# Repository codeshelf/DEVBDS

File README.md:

# DEVBDS
All of the weird, awesome, strange and mundane dev boards one could ever hope to use.

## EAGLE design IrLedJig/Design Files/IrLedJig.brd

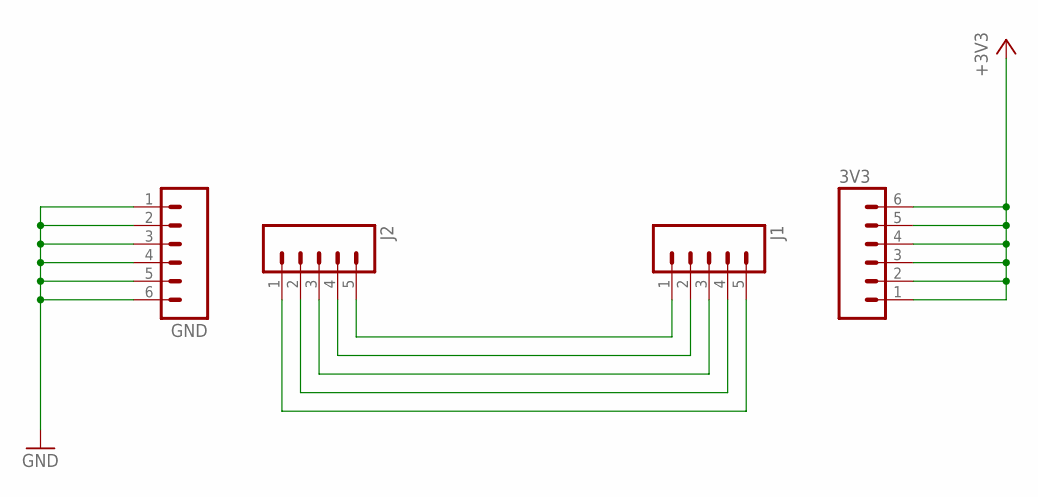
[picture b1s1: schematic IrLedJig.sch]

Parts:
3V3: M06LOCK; 1X06_LOCK
GND: M06LOCK; 1X06_LOCK
J1, J2: M05LOCK; 1X05_LOCK

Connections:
+3V3: 3V3.1, 3V3.2, 3V3.3, 3V3.4, 3V3.5, 3V3.6
GND: GND.1, GND.2, GND.3, GND.4, GND.5, GND.6
unnamed: J1.1, J2.5
unnamed: J1.2, J2.4
unnamed: J1.3, J2.3
unnamed: J1.4, J2.2
unnamed: J1.5, J2.1

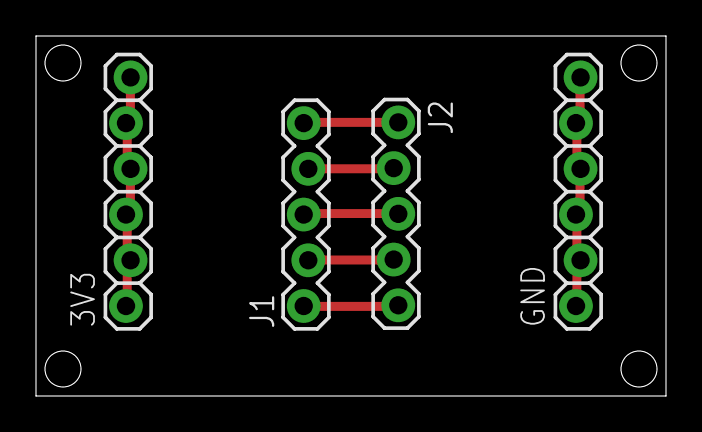
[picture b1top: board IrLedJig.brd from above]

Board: 2 copper layers, 35.0 x 20.0 mm, 4 parts (0 on the bottom side), 7 nets.

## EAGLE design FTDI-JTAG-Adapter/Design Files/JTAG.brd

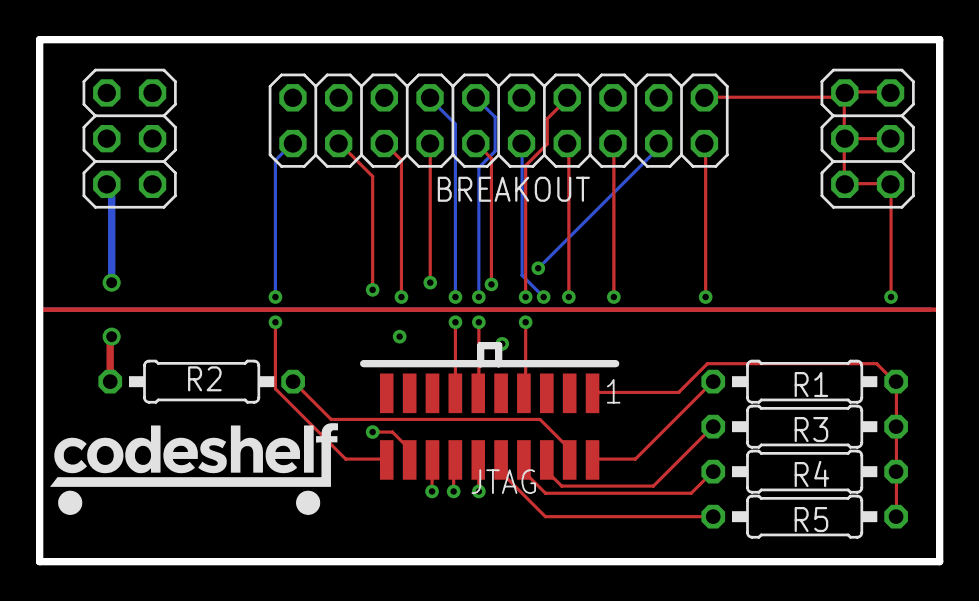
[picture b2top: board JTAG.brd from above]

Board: 4 copper layers, 50.0 x 29.0 mm, 10 parts (0 on the bottom side), 15 nets.

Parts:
3V3: 2X03
BREAKOUT: 2X10
GND: 2X03
JTAG: 2X10JTAGSMD; 2X10JTAG-SMD
R1, R2, R3, R4, R5: 0207/10
U$1: CODESHELF-LOGOSMALL; CODESHELF-LOGO-SMALL

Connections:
3V3: 3V3.1, 3V3.2, 3V3.3, 3V3.4, 3V3.5, 3V3.6, BREAKOUT.1, JTAG.P$1, R1.1, R3.1, R4.1, R5.1
GND: BREAKOUT.3, BREAKOUT.5, BREAKOUT.9, BREAKOUT.15, BREAKOUT.17, BREAKOUT.19, GND.1, GND.2, GND.3, GND.4, GND.5, GND.6, JTAG.P$3, JTAG.P$5, JTAG.P$9, JTAG.P$15, JTAG.P$17, JTAG.P$19, R2.1
unnamed: BREAKOUT.2, JTAG.P$2, R1.2
unnamed: BREAKOUT.4, JTAG.P$4, R2.2
unnamed: BREAKOUT.6, JTAG.P$6, R3.2
unnamed: BREAKOUT.8, JTAG.P$8, R4.2
unnamed: BREAKOUT.10, JTAG.P$10, R5.2
unnamed: BREAKOUT.12, JTAG.P$12
unnamed: BREAKOUT.14, JTAG.P$14
unnamed: BREAKOUT.16, JTAG.P$16
unnamed: BREAKOUT.18, JTAG.P$18
unnamed: BREAKOUT.20, JTAG.P$20
unnamed: BREAKOUT.7, JTAG.P$7
unnamed: BREAKOUT.11, JTAG.P$11
unnamed: BREAKOUT.13, JTAG.P$13

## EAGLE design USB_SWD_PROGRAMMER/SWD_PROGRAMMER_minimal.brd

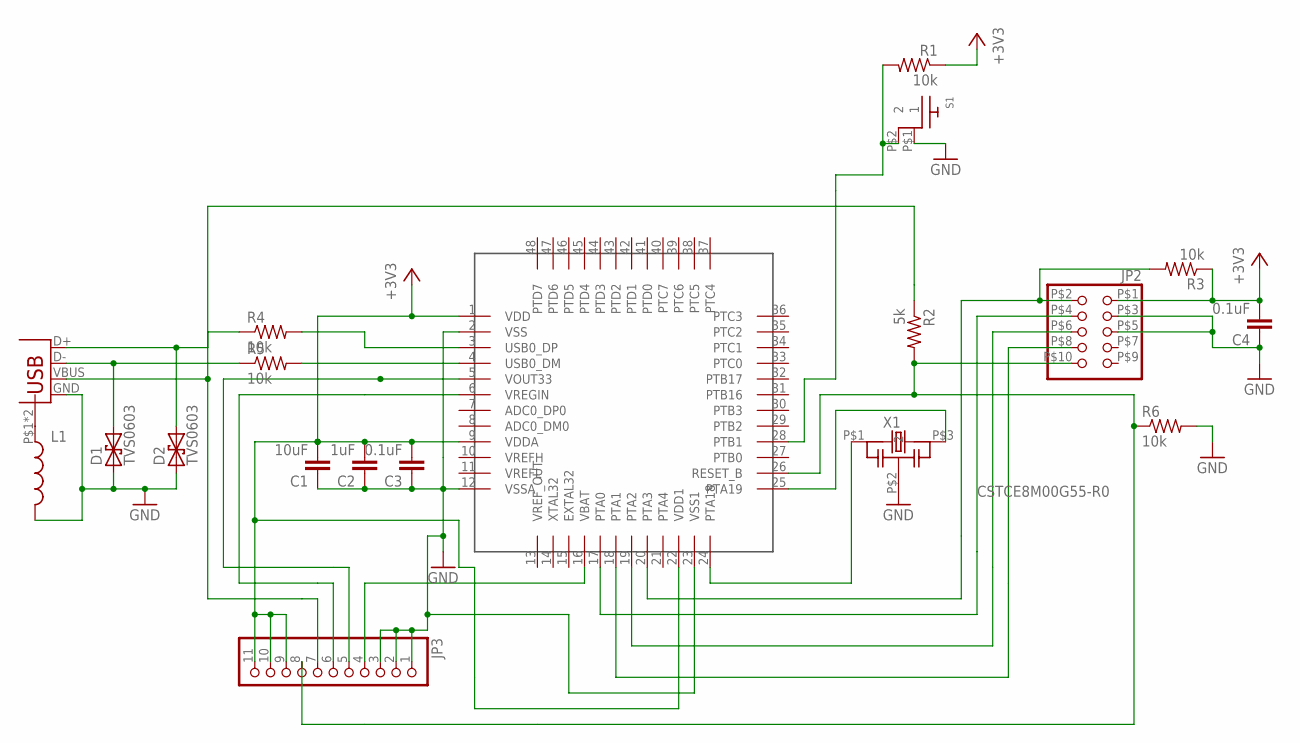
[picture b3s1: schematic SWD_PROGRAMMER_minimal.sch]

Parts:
C1: 10uF; C0805
C2: 1uF; C0805
C3, C4: 0.1uF; C0805
D1, D2: TVS0603; 0603-RES
J1: USB_B; USB-B-PTH-VERTICAL
JP2: PINHD-2X5SMALL; 2X5HDR
JP3: PINHD-1X11; 1X11
L1: INDUCTOR0603; 0603
R1, R3, R4, R5, R6: 10k; RF-C0805
R2: 5k; RF-C0805
S1: RA_BUTTON
U$1: KL20_48; LQFP-48
X1: CSTCE8M00G55-R0; CSTCE_G_A

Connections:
+3V3: C1.2, C2.2, C3.2, C4.2, JP2.P$1 (1), JP3.9, JP3.10, JP3.11, R1.1, R3.1, U$1.1 (VDD), U$1.9 (VDDA), U$1.22 (VDD1)
CLK: JP2.P$4 (4), U$1.17 (PTA0)
D_N: D1.2, J1.D-, R5.1
D_P: D2.2, J1.D+, R4.1
GND: C1.1, C2.1, C3.1, C4.1, D1.1, D2.1, J1.GND, JP2.P$3 (3), JP2.P$5 (5), JP3.1, JP3.2, JP3.3, L1.2, R6.2, S1.P$1 (1), U$1.2 (VSS), U$1.12 (VSSA), U$1.23 (VSS1), X1.P$2 (2)
JRST: JP2.P$10 (10), JP3.8, R2.2, R6.1, U$1.26 (RESET_B)
unnamed: R4.2, U$1.3 (USB0_DP)
unnamed: J1.VBUS, JP3.7, R2.1
unnamed: JP3.4, U$1.16 (VBAT)
unnamed: U$1.24 (PTA18), X1.P$1 (1)
unnamed: J1.P$1 (SHIELD), J1.P$2 (SHIELD), L1.1
unnamed: U$1.25 (PTA19), X1.P$3 (3)
unnamed: JP3.5, U$1.5 (VOUT33)
unnamed: JP3.6, U$1.6 (VREGIN)
unnamed: R5.2, U$1.4 (USB0_DM)
RST: R1.2, S1.P$2 (2), U$1.28 (PTB1)
TDI: JP2.P$8 (8), U$1.18 (PTA1)
TDO: JP2.P$6 (6), U$1.19 (PTA2)
TMS: JP2.P$2 (2), R3.2, U$1.20 (PTA3)

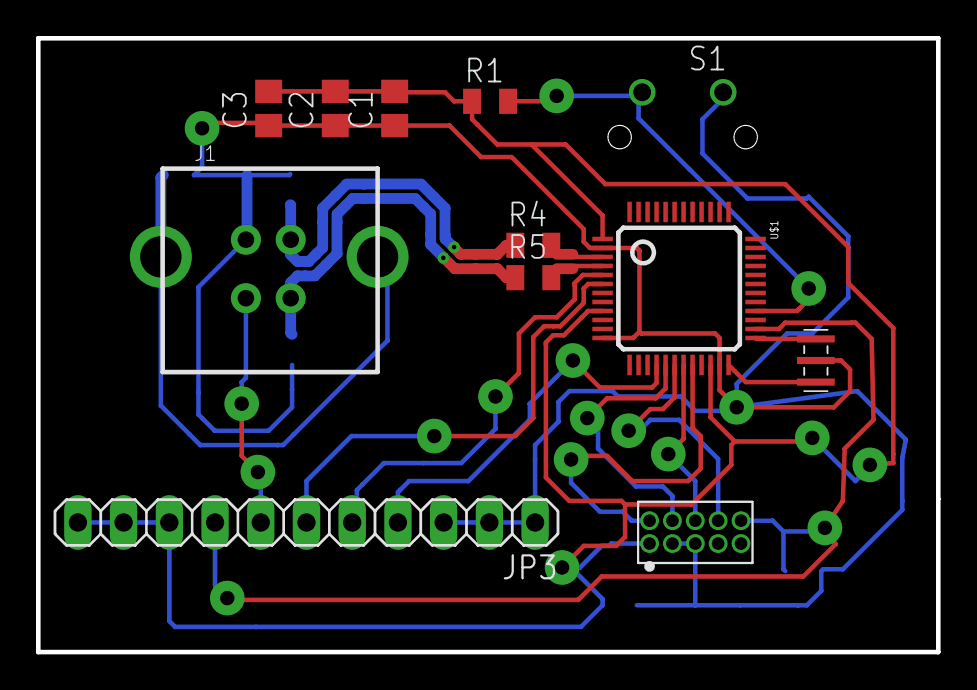
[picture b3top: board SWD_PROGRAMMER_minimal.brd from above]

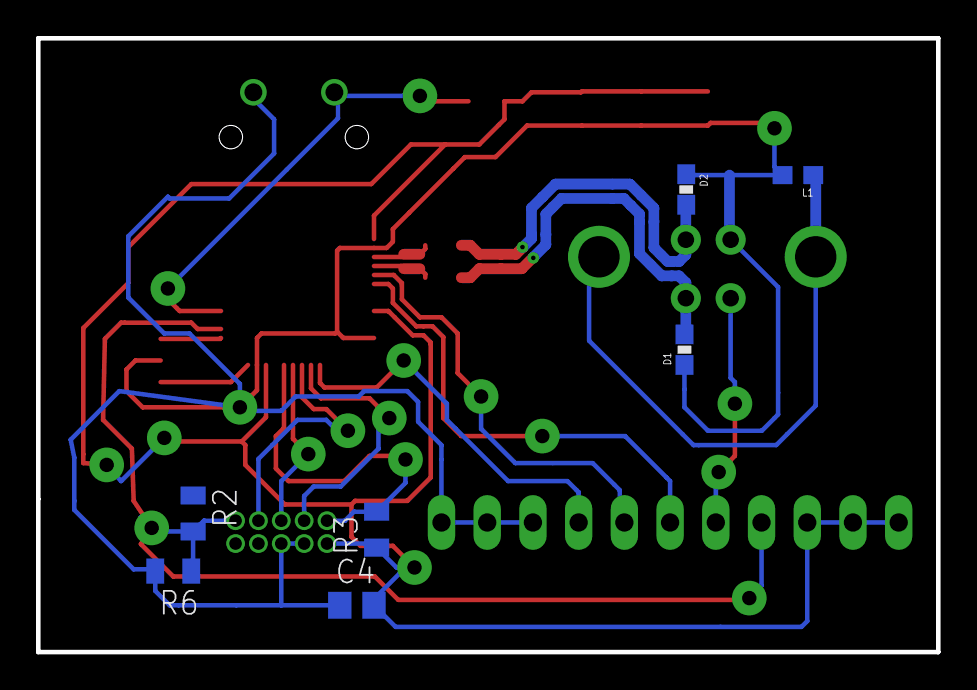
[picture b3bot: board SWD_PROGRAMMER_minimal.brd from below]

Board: 2 copper layers, 50.0 x 34.1 mm, 19 parts (7 on the bottom side), 19 nets.

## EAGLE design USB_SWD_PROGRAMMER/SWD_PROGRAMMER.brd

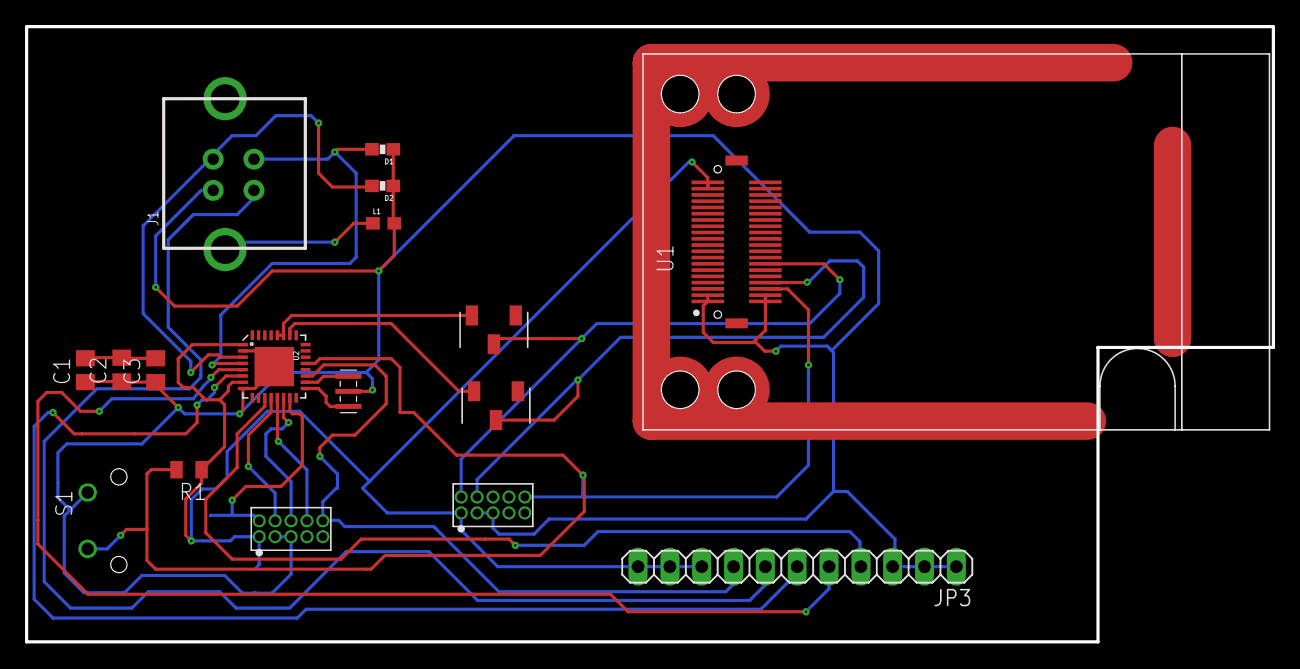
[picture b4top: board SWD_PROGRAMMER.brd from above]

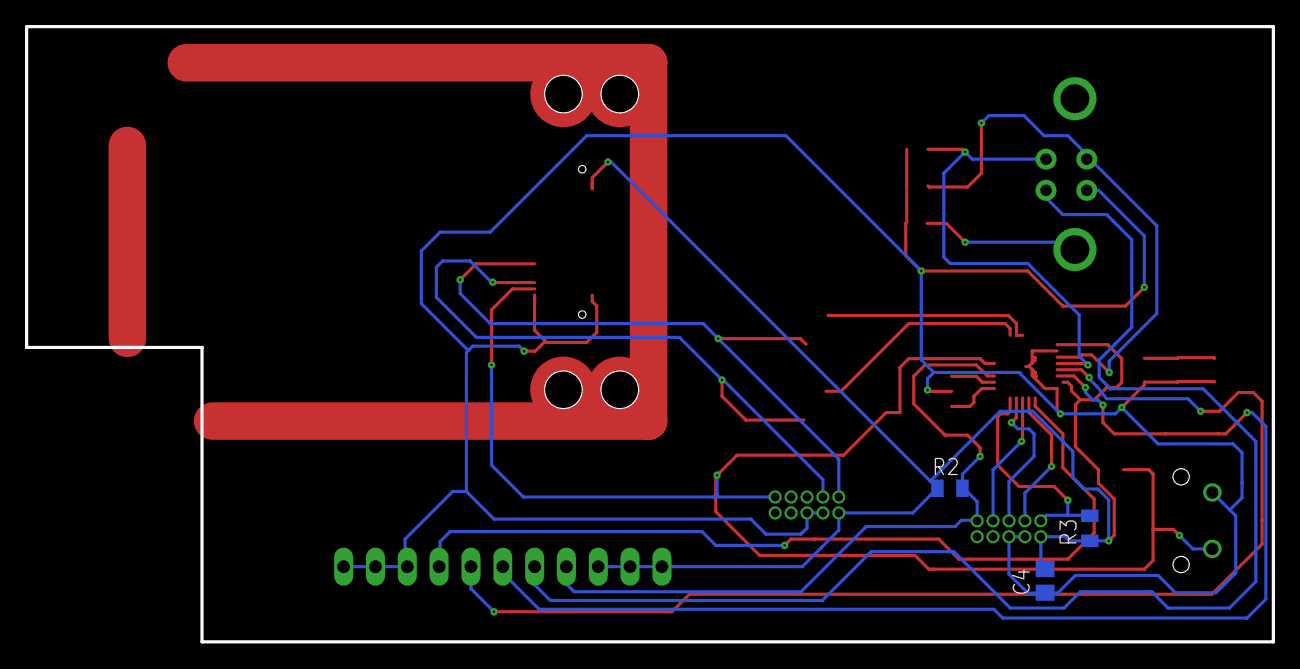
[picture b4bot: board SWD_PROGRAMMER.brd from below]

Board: 2 copper layers, 99.5 x 49.1 mm, 20 parts (3 on the bottom side), 21 nets.

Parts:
C1: 10uF; C0805
C2: 1uF; C0805
C3, C4: 0.1uF; C0805
D1, D2: TVS0603; 0603-RES
J1: USB_B; USB-B-PTH-VERTICAL
JP1, JP2: 2X5HDR
JP3: 1X11
L1: 0603
R1, R2, R3: 10k; RF-C0805
S1: RA_BUTTON
SW1, SW2: CJS
U1: KW2_CPU_OFFSET; BRAIN_OFFSET
U2: KL20PAD; QFN-32
X1: CSTCE8M00G55-R0; CSTCE_G_A

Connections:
+3V3: C1.2, C2.2, C3.2, C4.2, JP1.P$1, JP2.P$1, JP3.9, JP3.10, JP3.11, R1.1, R2.1, R3.1, U1.P$37, U1.P$39, U2.1, U2.7
CLK: JP2.P$4, U2.12
GND: C1.1, C2.1, C3.1, C4.1, D1.1, D2.1, J1.GND, JP1.P$3, JP1.P$5, JP2.P$3, JP2.P$5, JP3.1, JP3.2, JP3.3, L1.2, S1.P$1, U1.P$1, U1.P$2, U1.P$3, U1.P$4, U2.2, U2.8, U2.EP, X1.P$2
JRST: JP2.P$10, JP3.8, R2.2, U2.19
unnamed: SW1.P$3, U2.27, U2.28
unnamed: J1.VBUS, JP3.7
unnamed: JP3.4, U2.11
unnamed: U2.17, X1.P$1
unnamed: J1.P$1, J1.P$2, L1.1
unnamed: U2.18, X1.P$3
unnamed: JP3.5, U2.5
unnamed: JP3.6, U2.6
unnamed: D1.2, J1.D-, U2.4
unnamed: D2.2, J1.D+, U2.3
RST: JP1.P$10, R1.2, S1.P$2, U1.P$6, U2.21
SWD_CLK: JP1.P$4, SW2.P$1, U1.P$8
SWD_DIO: JP1.P$2, SW1.P$1, U1.P$14
SWD_TGT_CLK: SW2.P$3, U2.26
TDI: JP2.P$8, U2.13
TDO: JP2.P$6, U2.14
TMS: JP2.P$2, R3.2, U2.15

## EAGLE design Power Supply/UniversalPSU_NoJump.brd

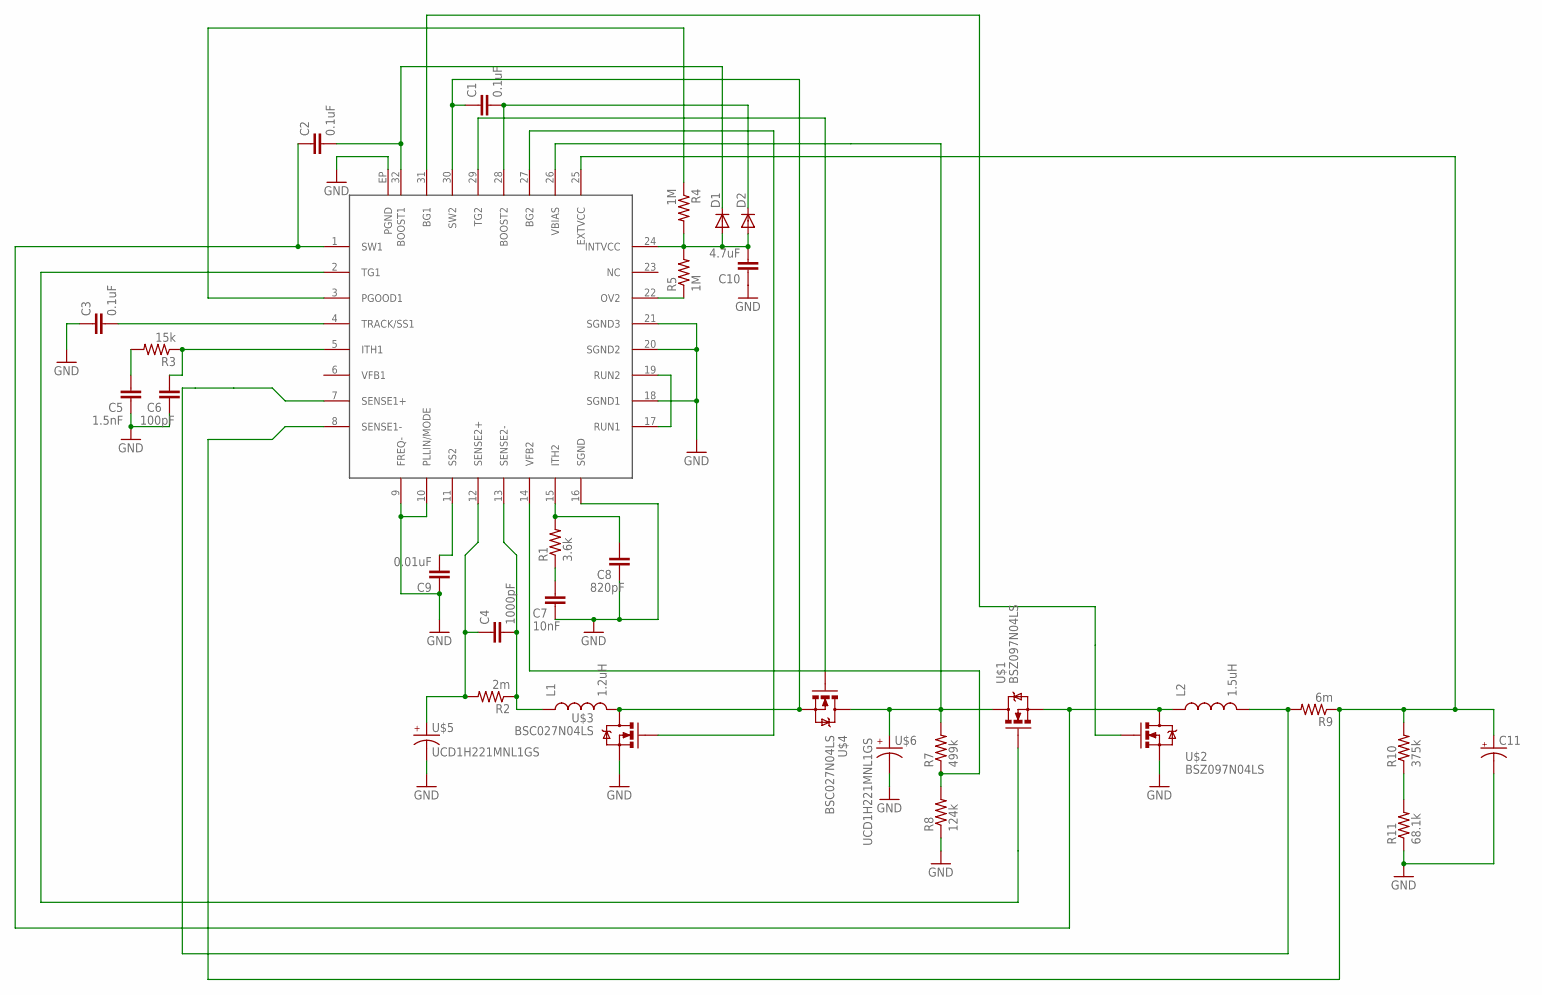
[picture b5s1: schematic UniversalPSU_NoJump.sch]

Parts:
C1, C2, C3: 0.1uF; C0805
C4: 1000pF; C0805
C5: 1.5nF; C0805
C6: 100pF; C0805
C7: 10nF; C0805
C8: 820pF; C0805
C9: 0.01uF; C0805
C10: 4.7uF; C0805
C11: CAP_POL7343; EIA7343
D1, D2: DIODESOD; SOD-323
L1: 1.2uH; 744325120
L2: 1.5uH; 744314150
R1: 3.6k; RF-C0805
R2: 2m; 1206
R3: 15k; RF-C0805
R4, R5: 1M; RF-C0805
R7: 499k; RF-C0805
R8: 124k; RF-C0805
R9: 6m; 1206
R10: 375k; RF-C0805
R11: 68.1k; RF-C0805
U1: LTC7812; QFN-32_UH
U$1, U$2: BSZ097N04LS; PG-TSDSON-8
U$3, U$4: BSC027N04LS; PG-TSDSON-8
U$5, U$6: UCD1H221MNL1GS; 10X10CAP

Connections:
GND: C3.1, C5.1, C6.1, C7.1, C8.1, C9.1, C10.1, C11.C (-), R8.1, R11.1, U1.9 (FREQ-), U1.10 (PLLIN/MODE), U1.16 (SGND), U1.18 (SGND1), U1.20 (SGND2), U1.21 (SGND3), U1.EP (PGND), U$2.P$1 (S), U$2.P$2 (S), U$2.P$3 (S), U$3.P$1 (S), U$3.P$2 (S), U$3.P$3 (S), U$5.P$1 (2), U$6.P$1 (2)
unnamed: C3.2, U1.4 (TRACK/SS1)
unnamed: C2.2, D1.1 (C), U1.32 (BOOST1)
unnamed: C2.1, L2.P$1 (1), U1.1 (SW1), U$1.P$1 (S), U$1.P$2 (S), U$1.P$3 (S), U$2.P$5 (D)
unnamed: C1.2, D2.1 (C), U1.28 (BOOST2)
unnamed: C1.1, L1.P$2 (2), U1.30 (SW2), U$3.P$5 (D), U$4.P$1 (S), U$4.P$2 (S), U$4.P$3 (S)
unnamed: C8.2, R1.2, U1.15 (ITH2)
unnamed: C4.2, L1.P$1 (1), R2.1, U1.13 (SENSE2-)
unnamed: C4.1, R2.2, U1.12 (SENSE2+), U$5.P$2 (1)
unnamed: C6.2, R3.1, U1.5 (ITH1)
unnamed: C5.2, R3.2
unnamed: C7.2, R1.1
unnamed: R5.1, U1.22 (OV2)
unnamed: C9.2, U1.11 (SS2)
unnamed: R4.1, U1.3 (PGOOD1)
unnamed: L2.P$2 (2), R9.2, U1.7 (SENSE1+)
unnamed: C11.A (+), R9.1, R10.2, U1.8 (SENSE1-), U1.25 (EXTVCC)
unnamed: C10.2, D1.2 (A), D2.2 (A), R4.2, R5.2, U1.24 (INTVCC)
unnamed: U1.27 (BG2), U$3.P$4 (G)
unnamed: U1.29 (TG2), U$4.P$4 (G)
unnamed: U1.17 (RUN1), U1.19 (RUN2)
unnamed: R7.2, U1.26 (VBIAS), U$1.P$5 (D), U$4.P$5 (D), U$6.P$2 (1)
unnamed: R7.1, R8.2, U1.14 (VFB2)
unnamed: U1.2 (TG1), U$1.P$4 (G)
unnamed: U1.31 (BG1), U$2.P$4 (G)
unnamed: R10.1, R11.2

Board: 2 copper layers, 32 parts (27 on the bottom side), 26 nets, no tracks yet.

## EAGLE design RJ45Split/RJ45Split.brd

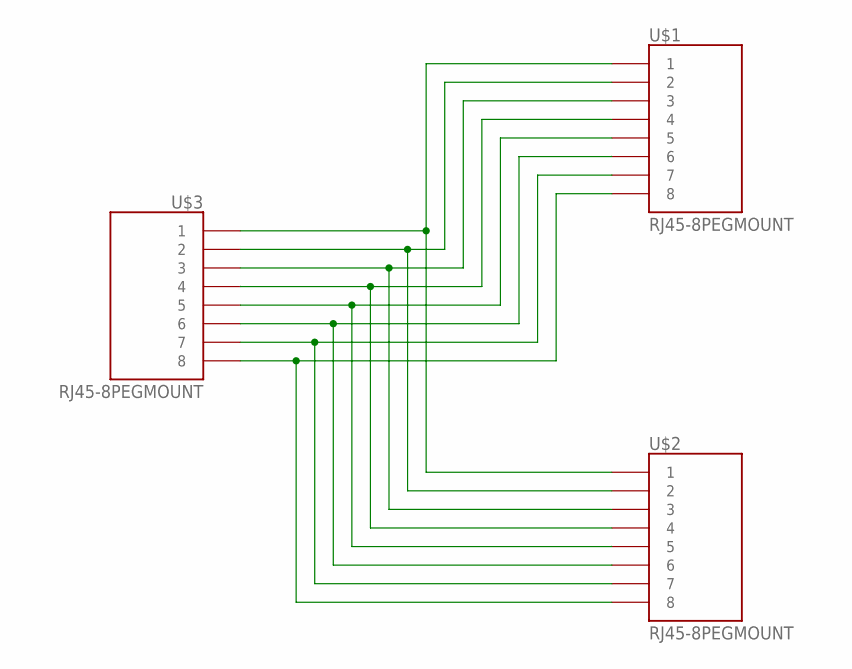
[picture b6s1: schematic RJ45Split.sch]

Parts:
U$1, U$2, U$3: RJ45-8PEGMOUNT; MOLEX-0955016889

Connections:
unnamed: U$1.P$1 (1), U$2.P$1 (1), U$3.P$1 (1)
unnamed: U$1.P$2 (2), U$2.P$2 (2), U$3.P$2 (2)
unnamed: U$1.P$3 (3), U$2.P$3 (3), U$3.P$3 (3)
unnamed: U$1.P$4 (4), U$2.P$4 (4), U$3.P$4 (4)
unnamed: U$1.P$5 (5), U$2.P$5 (5), U$3.P$5 (5)
unnamed: U$1.P$6 (6), U$2.P$6 (6), U$3.P$6 (6)
unnamed: U$1.P$7 (7), U$2.P$7 (7), U$3.P$7 (7)
unnamed: U$1.P$8 (8), U$2.P$8 (8), U$3.P$8 (8)

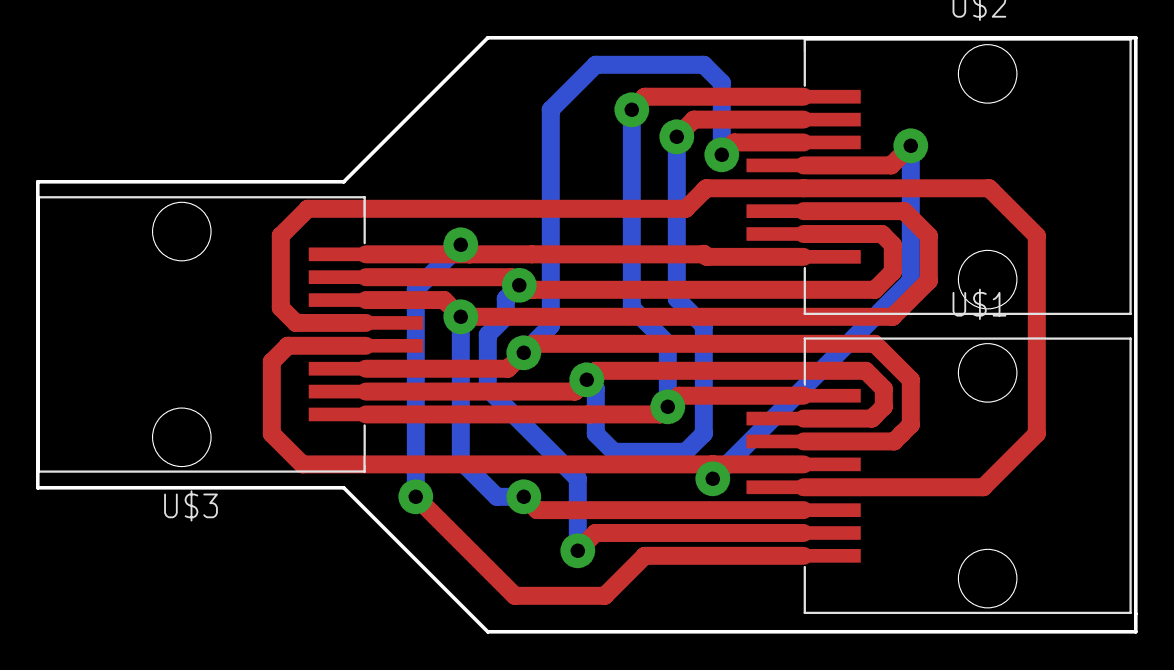
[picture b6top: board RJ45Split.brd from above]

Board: 2 copper layers, 61.0 x 33.0 mm, 3 parts (0 on the bottom side), 8 nets.

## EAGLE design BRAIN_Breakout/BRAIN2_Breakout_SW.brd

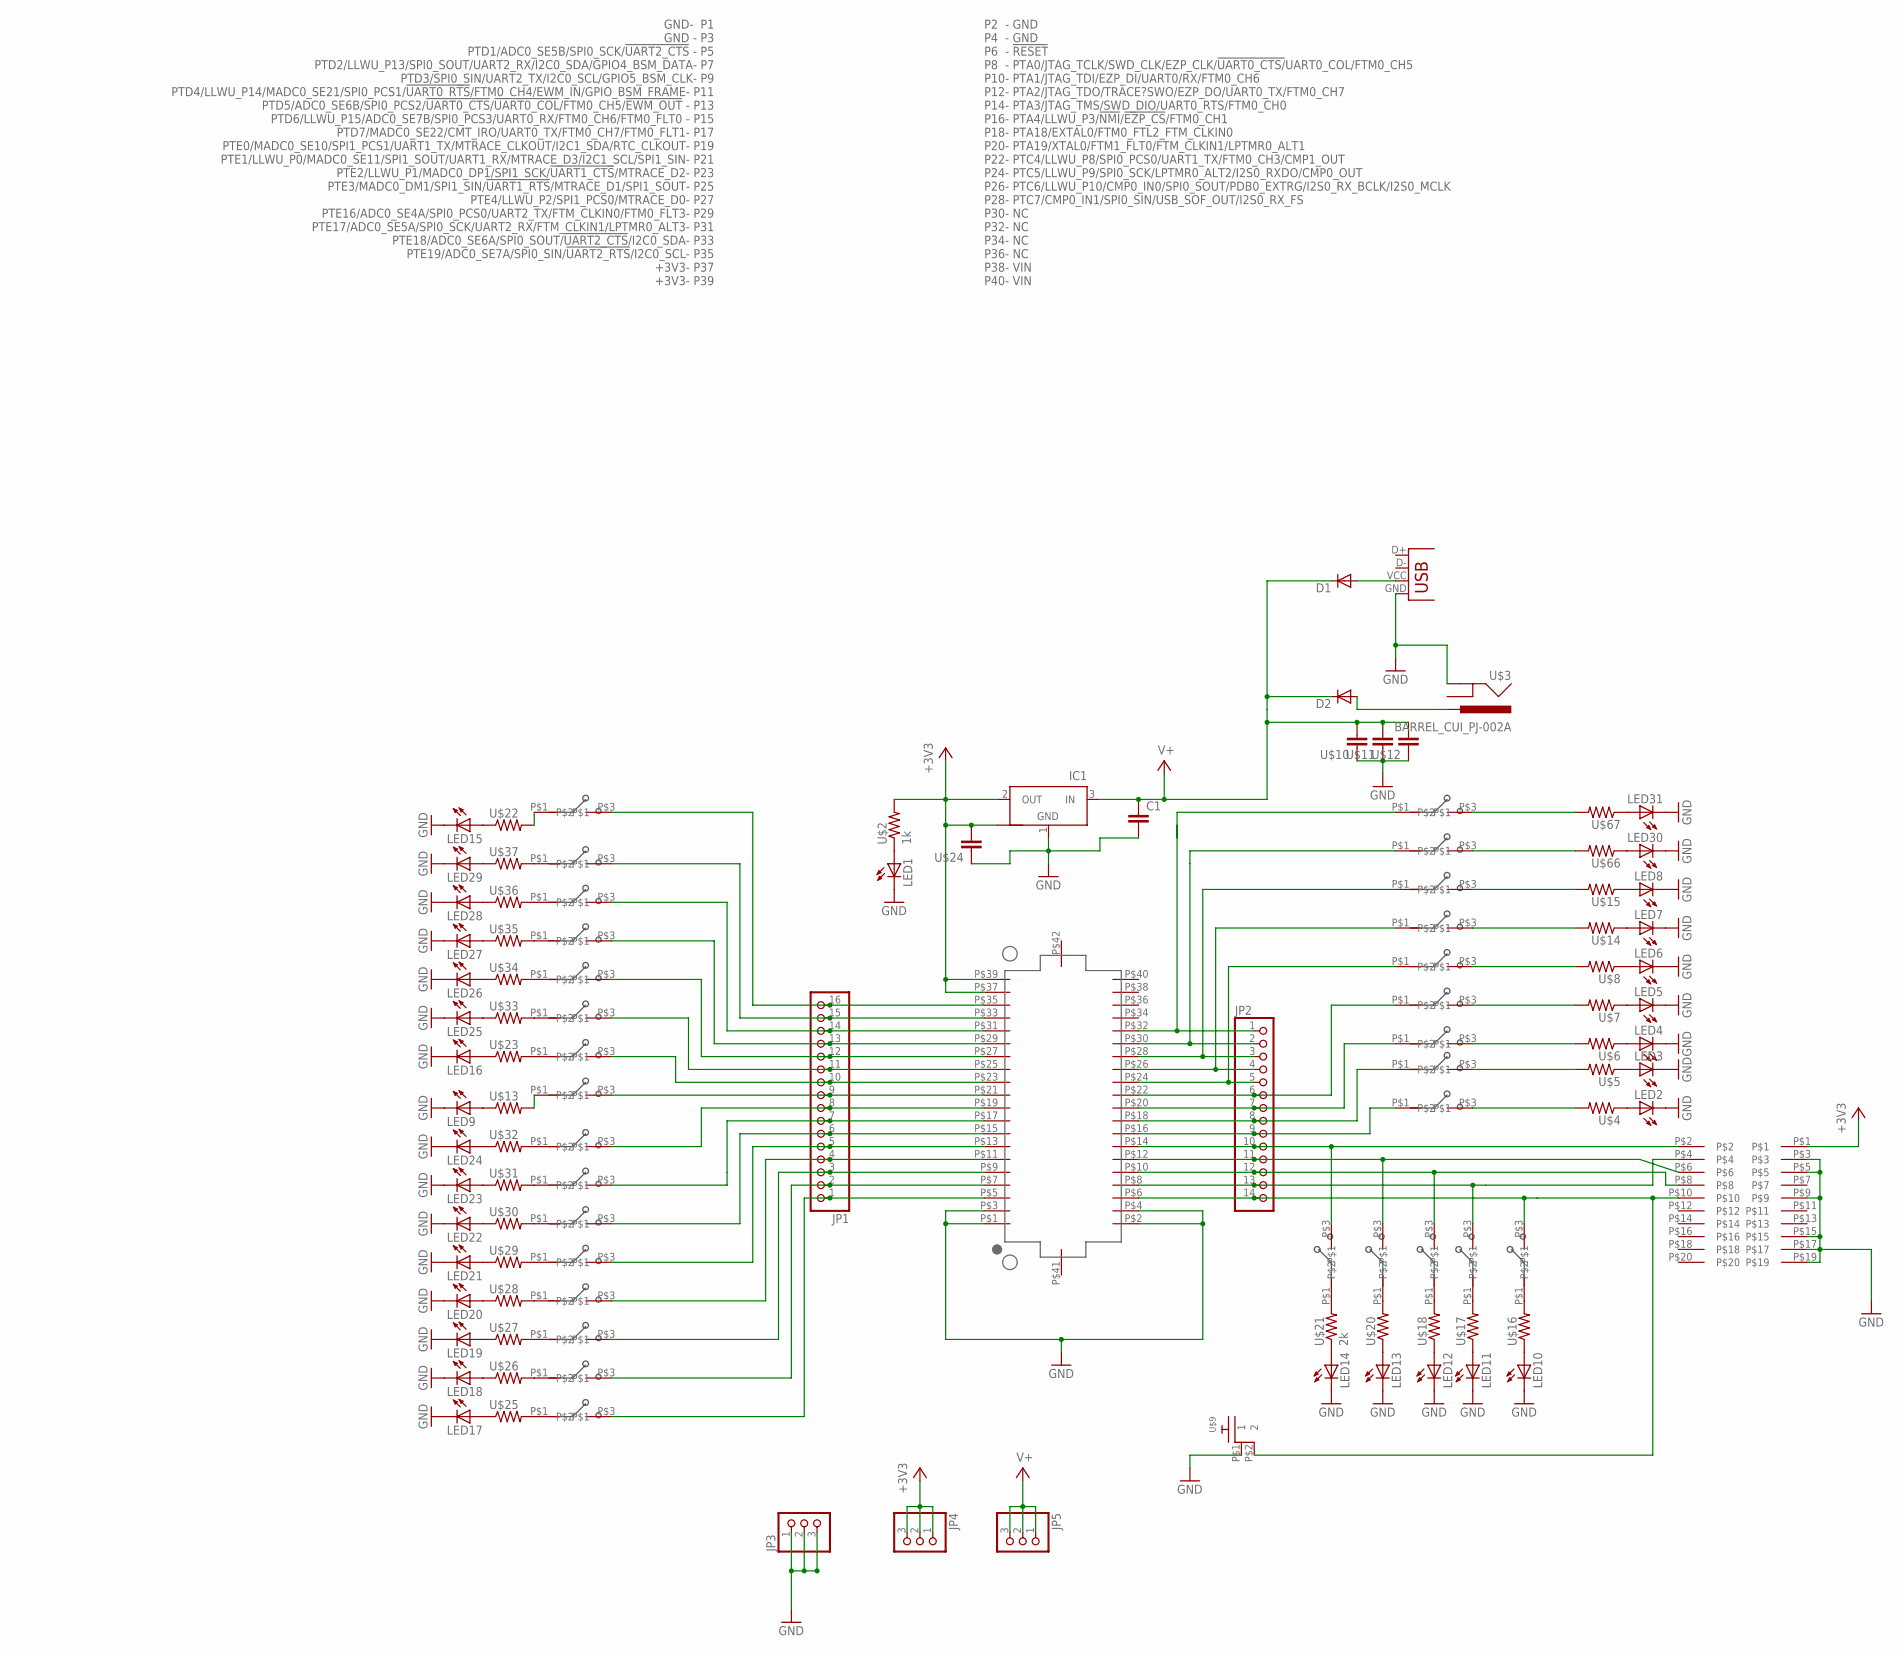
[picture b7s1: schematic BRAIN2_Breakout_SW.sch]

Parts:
C1: RF-C0805; C0805
D1, D2: DIODESMA; SMA-DIODE
IC1: NCP1117ST33T3G_1; SOT223
JP1: PINHD-1X16; 1X16
JP2: PINHD-1X14; 1X14
JP3, JP4, JP5: PINHD-1X3; 1X03
LED1, LED2, LED3, LED4, LED5, LED6, LED7, LED8, LED9, LED10, LED11, LED12, LED13, LED14, LED15, LED16, LED17, LED18, LED19, LED20, LED21, LED22, LED23, LED24, LED25, LED26, LED27, LED28, LED29, LED30, LED31: LEDCHIP-LED0805; CHIP-LED0805
U$1: KW2_CPU_NEW; BRAIN_NEW
U$2: 1k; RF-C0805
U$3: BARREL_CUI_PJ-002A
U$4, U$5, U$6, U$7, U$8, U$13, U$14, U$15, U$16, U$17, U$18, U$20, U$22, U$23, U$25, U$26, U$27, U$28, U$29, U$30, U$31, U$32, U$33, U$34, U$35, U$36, U$37, U$66, U$67: RF-R0805; RF-C0805
U$9: RA_BUTTON
U$10, U$11, U$12, U$24: RF-C0805; C0805
U$19: 2X10JTAG
U$21: 2k; RF-C0805
U$38, U$39, U$40, U$41, U$42, U$43, U$44, U$45, U$46, U$47, U$48, U$49, U$50, U$51, U$52, U$53, U$54, U$55, U$56, U$57, U$58, U$59, U$60, U$61, U$62, U$63, U$64, U$65, U$68, U$69: CJS
X1: USB; USB3076-30-A

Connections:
+3V3: IC1.2 (OUT), IC1.4 (OUT1), JP4.1, JP4.2, JP4.3, U$1.P$37 (+3V3), U$1.P$39 (+3V3), U$2.2, U$19.P$1, U$24.2
GND: C1.2, IC1.1 (GND), JP3.1, JP3.2, JP3.3, LED1.C, LED2.C, LED3.C, LED4.C, LED5.C, LED6.C, LED7.C, LED8.C, LED9.C, LED10.C, LED11.C, LED12.C, LED13.C, LED14.C, LED15.C, LED16.C, LED17.C, LED18.C, LED19.C, LED20.C, LED21.C, LED22.C, LED23.C, LED24.C, LED25.C, LED26.C, LED27.C, LED28.C, LED29.C, LED30.C, LED31.C, U$1.P$1 (GND), U$1.P$2 (GND), U$1.P$3 (GND), U$1.P$4 (GND), U$3.P$2 (GND), U$9.P$1 (1), U$10.1, U$11.1, U$12.1, U$19.P$3, U$19.P$5, U$19.P$9, U$19.P$15, U$19.P$17, U$19.P$19, U$24.1, X1.GND, X1.P$4
unnamed: LED1.A, U$2.1
unnamed: LED2.A, U$4.1
unnamed: LED3.A, U$5.1
unnamed: LED4.A, U$6.1
unnamed: LED8.A, U$15.1
unnamed: LED5.A, U$7.1
unnamed: LED6.A, U$8.1
unnamed: LED7.A, U$14.1
unnamed: LED9.A, U$13.1
unnamed: U$13.2, U$44.P$1
unnamed: U$15.2, U$65.P$3
unnamed: U$14.2, U$64.P$3
unnamed: U$8.2, U$63.P$3
unnamed: U$7.2, U$62.P$3
unnamed: U$6.2, U$61.P$3
unnamed: U$5.2, U$60.P$3
unnamed: U$4.2, U$59.P$3
unnamed: U$25.2, U$38.P$1
unnamed: U$26.2, U$39.P$1
unnamed: U$27.2, U$40.P$1
unnamed: JP2.3, U$1.P$28 (PTC7/CMP0_IN1/SPI0_SIN/USB_SOF_OUT/I2S0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), U$65.P$1
unnamed: JP2.4, U$1.P$26 (PTC6/LLWU_P10/CMP0_IN0/SPI0_SOUT/PDB0_E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), U$64.P$1
unnamed: JP2.5, U$1.P$24 (PTC5/LLWU_P8/SPI0_PCS0/UART1_TX/FTM0_CH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), U$63.P$1
unnamed: JP2.6, U$1.P$22 (PTC4/LLWU_P8/SPI0_PCS0/UART1_TX/FTM0_CH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), U$62.P$1
unnamed: JP2.7, U$1.P$20 (PTA19/XTAL0/FTM1_FLT0/FTM_CLKIN1/LPTMR0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), U$61.P$1
unnamed: JP2.8, U$1.P$18 (PTA18/EXTAL0/FTM0_FTL2_FTM_CLKIN0), U$60.P$1
unnamed: JP2.9, U$1.P$16 (PTA4/LLWU_P3/!NMI!/!EZP_CS!/FTM0_CH1), U$59.P$1
unnamed: LED15.A, U$22.1
unnamed: LED17.A, U$25.1
unnamed: LED18.A, U$26.1
unnamed: LED19.A, U$27.1
unnamed: LED20.A, U$28.1
unnamed: LED16.A, U$23.1
unnamed: LED25.A, U$33.1
unnamed: LED26.A, U$34.1
unnamed: LED27.A, U$35.1
unnamed: LED21.A, U$29.1
unnamed: LED22.A, U$30.1
unnamed: LED23.A, U$31.1
unnamed: LED24.A, U$32.1
unnamed: U$28.2, U$41.P$1
unnamed: U$29.2, U$42.P$1
unnamed: U$31.2, U$43.P$1
unnamed: U$37.2, U$46.P$1
unnamed: U$36.2, U$47.P$1
unnamed: LED28.A, U$36.1
unnamed: JP2.10, U$1.P$14 (PTA3/JTAG_TMS/SWD_DIO/UART0_RTS/FTM0_CH0), U$19.P$2, U$58.P$3
unnamed: LED10.A, U$16.1
unnamed: U$16.2, U$54.P$1
unnamed: LED11.A, U$17.1
unnamed: U$17.2, U$55.P$1
unnamed: JP2.12, U$1.P$10 (PTA1/JTAG_TDI/EZP_DI/UART0/RX/FTM0_CH6), U$19.P$8, U$56.P$3
unnamed: LED12.A, U$18.1
unnamed: U$18.2, U$56.P$1
unnamed: JP2.13, U$1.P$8 (PTA0/JTAG_TCLK/SWD_CLK/EZP_CLK/!UART0_C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), U$19.P$4, U$55.P$3
unnamed: LED13.A, U$20.1
unnamed: U$20.2, U$57.P$1
unnamed: JP2.14, U$1.P$6 (!RESET), U$9.P$2 (2), U$19.P$10, U$54.P$3
unnamed: LED14.A, U$21.1
unnamed: U$21.2, U$58.P$1
unnamed: LED29.A, U$37.1
unnamed: U$22.2, U$45.P$1
unnamed: U$35.2, U$48.P$1
unnamed: U$34.2, U$49.P$1
unnamed: U$33.2, U$50.P$1
unnamed: U$23.2, U$51.P$1
unnamed: U$32.2, U$52.P$1
unnamed: U$30.2, U$53.P$1
unnamed: D2.A, U$3.P$1 (PWR)
unnamed: D1.A, X1.VCC (VBUS)
unnamed: JP2.1, U$1.P$32 (NC), U$69.P$1
unnamed: LED30.A, U$66.1
unnamed: LED31.A, U$67.1
unnamed: U$67.2, U$69.P$3
unnamed: U$66.2, U$68.P$3
unnamed: JP2.2, U$1.P$30 (NC), U$68.P$1
unnamed: JP2.11, U$1.P$12 (PTA2/JTAG_TDO/TRACE?SWO/EZP_DO/UART0_TX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), U$19.P$6, U$57.P$3
PTD1: JP1.1, U$1.P$5 (PTD1/ADC0_SE5B/SPI0_SCK/!UART2_CTS), U$38.P$3
PTD2: JP1.2, U$1.P$7 (PTD2/LLWU_P13/SPI0_SOUT/UART2_RX/I2C0_S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), U$39.P$3
PTD3: JP1.3, U$1.P$9 (PTD3/SPI0_SIN/UART2_TX/I2C0_SCL/GPIO5_B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), U$40.P$3
PTD4: JP1.4, U$1.P$11 (PTD4/LLWU_P14/MADC0_SE21/SPI0_PCS1/!UAR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), U$41.P$3
PTD5: JP1.5, U$1.P$13 (PTD5/ADC0_SE6B/SPI0_PCS2/!UART0_CTS!/!U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), U$42.P$3
PTD6: JP1.6, U$1.P$15 (PTD6/LLWU_P15/ADC0_SE7B/SPI0_PCS3/UART0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), U$53.P$3
PTD7: JP1.7, U$1.P$17 (PTD7/MADC0_SE22/CMT_IRO/UART0_TX/FTM0_C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), U$43.P$3
PTE0: JP1.8, U$1.P$19 (PTE0/MADC0_SE10/SPI1_PCS1/UART1_TX/MTRA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), U$52.P$3
PTE1: JP1.9, U$1.P$21 (PTE1/LLWU_P0/MADC0_SE11/SPI1_SOUT/UART1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), U$44.P$3
PTE2: JP1.10, U$1.P$23 (PTE2/LLWU_P1/MADC0_DP1/SPI1_SCK/!UART1_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), U$51.P$3
PTE3: JP1.11, U$1.P$25 (PTE3/MADC0_DM1/SPI1_SIN/!UART1_RTS!/MTR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), U$50.P$3
PTE4: JP1.12, U$1.P$27 (PTE4/LLWU_P2/SPI1_PCS0/MTRACE_D0), U$49.P$3
PTE16: JP1.13, U$1.P$29 (PTE16/ADC0_SE4A/SPI0_PCS0/UART2_TX/FTM_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), U$48.P$3
PTE17: JP1.14, U$1.P$31 (PTE17/ADC0_SE5A/SPI0_SCK/UART2_RX/FTM_C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), U$47.P$3
PTE18: JP1.15, U$1.P$33 (PTE18/ADC0_SE6A/SPI0_SOUT/!UART2_CTS!/I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), U$46.P$3
PTE19: JP1.16, U$1.P$35 (PTE19/ADC0_SE7A/SPI0_SIN/!UART2_RTS!/I2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), U$45.P$3
V+: C1.1, D1.C, D2.C, IC1.3 (IN), JP5.1, JP5.2, JP5.3, U$10.2, U$11.2, U$12.2

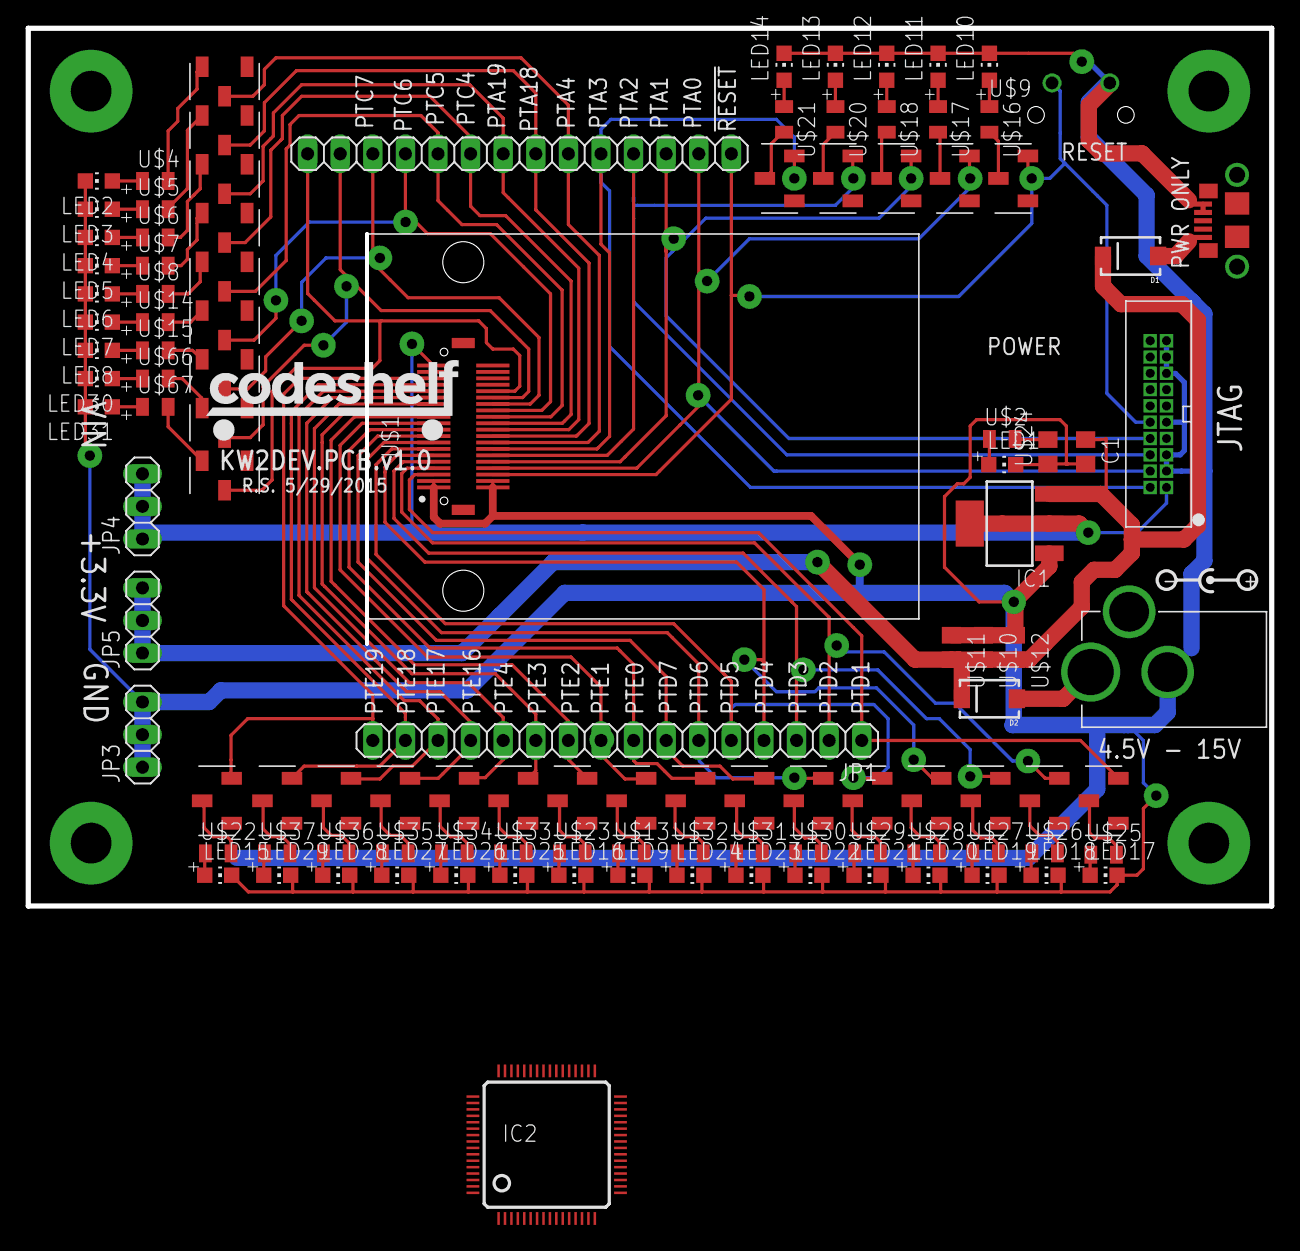
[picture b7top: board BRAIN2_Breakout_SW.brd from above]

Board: 2 copper layers, 96.9 x 68.4 mm, 111 parts (0 on the bottom side), 96 nets.

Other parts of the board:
IC2: FT2232HL; LQFP64

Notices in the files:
parts and their libraries:
SparkFun: Licensing: CC v3.0 Share-Alike You are welcome to use this library for commercial purposes.
